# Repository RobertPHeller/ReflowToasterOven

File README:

This project is based on the Instructables "Hack a Toaster Oven for Reflow
Soldering" by frank26080115 at
https://www.instructables.com/id/Hack-a-Toaster-Oven-for-Reflow-Soldering/

Notable differences:

1) It uses an ArduinoUno as the processing element and all of the electronics 
(except the display, pushbuttons, buzzer, and relay) are mounted on an 
Adafruit Proto Shield -- all of the components are through-hole components.

There is a KiCAD project here. It includes a "four layer" board. Actually I
have no intention of creating a "four layer" PCB. I intend to build this on an
Adafruit protoshield (Product #2077). The PCB I "designed" with KiCAD is a
mock up for the Adafruit protoshield (almost). The red and green layers
represent the wiring already on the protoshield, and includes the bus strips.
The blue and white "layers" represent the added wiring. The board also
provides the approximate component placement. For those people without KiCAD
installed, I have included a PDF of the schematic in the file
ReflowToasterOven.pdf and some "pictures" of the board in the BoardPictures
folder (one is a screen shot of the KiCAD PCB layout and the others are from
the 3D viewer).

2) Everything is mounted in a pair of plastic boxes and instead of "hacking"
an extension code, an AC power entry module and a pair of AC Receptacles are
used.

There are three files related to the mechanical construction:

ReflowToasterOven-mech.tcl
ReflowToasterOven-mech.gcad
ReflowToasterOven-mech.dxf

ReflowToasterOven-mech.tcl is a Tcl program that generates the 
ReflowToasterOven-mech.gcad file, which is the input for the GCAD3D program.  
The ReflowToasterOven-mech.dxf is a DXF file, that can be imported to any 3D 
cad program.

3) An Adafruit 1.8" *Color* TFT LCD SPI display is used, using Adafruit's 
graphics library.

4) The software is a "standard" Arduino project.

And the code lives in the ReflowToasterOven subdirectory. It compiles
successfully and just fits in the Uno's flash memory and only 1/2 of the SRAM
is used by static variables, leaving just under 1K for dynamic variables.

You will need to install the Adafruit ST7735 and Adafruit_GFX libraries from 
Adafruit's GitHub repo.  You will also need the MsTimer2 library 
(http://www.pjrc.com/teensy/td_libs_MsTimer2.html).

*Most* of the code is copied from the original program by frank26080115.  I 
modified things to use C++ classes and adapted to use the Arduino I/O 
libraries, the Adafruit ST7735-based TFT display and the MsTimer2 library.

I have not built or tested it yet.

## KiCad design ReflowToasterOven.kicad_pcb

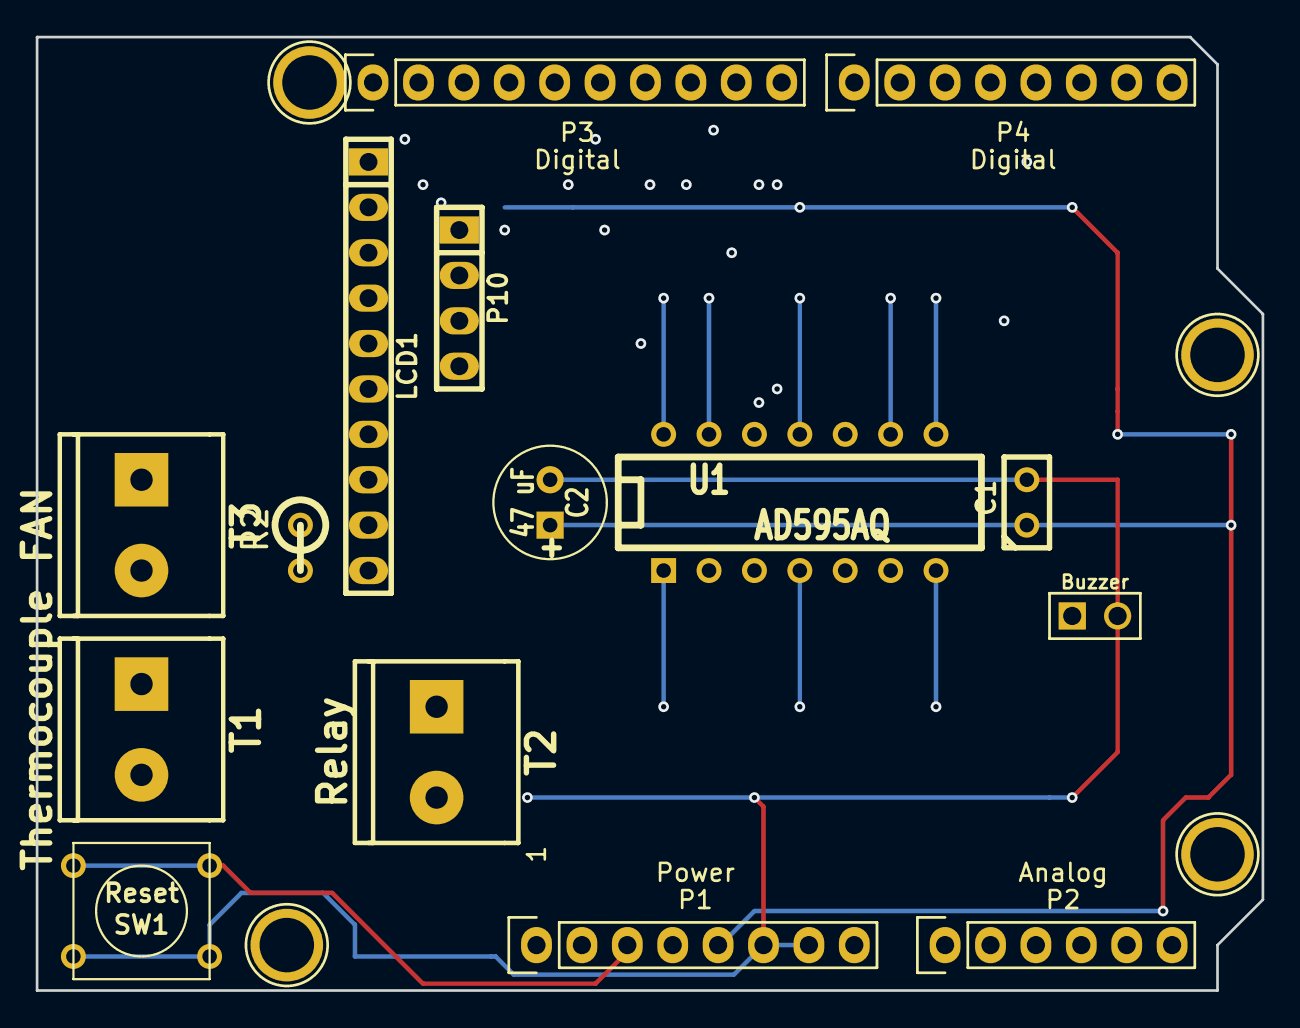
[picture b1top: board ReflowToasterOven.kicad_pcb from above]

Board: 4 copper layers, 68.6 x 53.3 mm, 19 parts (0 on the bottom side), 21 nets.

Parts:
C1: .1 uF; C1
C2: 47 uF; C1V7
LCD1: 160X128_TFT_DISPLAY; pin_strip_10
P1: Power; Socket_Strip_Arduino_1x08
P2: Analog; Socket_Strip_Arduino_1x06
P3: Digital; Socket_Strip_Arduino_1x10
P4: Digital; Socket_Strip_Arduino_1x08
P5, P6, P7, P8: CONN_01X01; Arduino_1pin
P9: Buzzer; PIN_ARRAY_2X1
P10: Switches; pin_strip_4
R2: 10K Ohms; R1
SW1: Reset; SW_PUSH_SMALL
T1: Thermocouple; mors_2p
T2: Relay; mors_2p
T3: FAN; mors_2p
U1: AD595AQ; DIP-14__300

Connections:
+3.3V: P1.4, P3.3
+5V: C1.1, C2.1, LCD1.9, P1.5, T3.1, U1.11
/A4(SDA): P2.5, P3.2
/A5(SCL): P2.6, P3.1
/Buzzer: P4.6, P9.1
/D/C: LCD1.7, P3.10
/Lite: LCD1.1, P4.5
/MISO: LCD1.2, P3.6
/MOSI: LCD1.4, P3.7
/Relay_Ctrl: P4.1, R2.1, T2.1
/Reset: P1.3, SW1.2
/SCK: LCD1.3, P3.5
/Switch1: P4.2, P10.1
/Switch2: P4.3, P10.2
/Switch3: P4.4, P10.3
/TFT_CS: LCD1.5, P3.8
/TFT_Reset: LCD1.8, P3.9
/Temp_Out: P2.1, U1.8, U1.9
GND: C1.2, C2.2, LCD1.10, P1.6, P1.7, P3.4, P9.2, P10.4, R2.2, SW1.1, T2.2, T3.2, U1.4, U1.7, U1.13
unnamed: T1.1, U1.1
unnamed: T1.2, U1.14

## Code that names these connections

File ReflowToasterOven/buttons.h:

// -!- c++ -!- //////////////////////////////////////////////////////////////
//
//  System        : 
//  Module        : 
//  Object Name   : $RCSfile$
//  Revision      : $Revision$
//  Date          : $Date$
//  Author        : $Author$
//  Created By    : Robert Heller
//  Created       : Sat Mar 24 13:23:58 2018
//  Last Modified : <180326.1313>
//
//  Description	
//
//  Notes
//
//  History
//	
/////////////////////////////////////////////////////////////////////////////
//
//    Copyright (C) 2018  Robert Heller D/B/A Deepwoods Software
//    (Portions Copyright (C) 2011 Frank Zhao)
//			51 Locke Hill Road
//			Wendell, MA 01379-9728
//
//    This program is free software; you can redistribute it and/or modify
//    it under the terms of the GNU General Public License as published by
//    the Free Software Foundation; either version 2 of the License, or
//    (at your option) any later version.
//
//    This program is distributed in the hope that it will be useful,
//    but WITHOUT ANY WARRANTY; without even the implied warranty of
//    MERCHANTABILITY or FITNESS FOR A PARTICULAR PURPOSE.  See the
//    GNU General Public License for more details.
//
//    You should have received a copy of the GNU General Public License
//    along with this program; if not, write to the Free Software
//    Foundation, Inc., 675 Mass Ave, Cambridge, MA 02139, USA.
//
// 
//
//////////////////////////////////////////////////////////////////////////////

#ifndef __BUTTONS_H
#define __BUTTONS_H
#define button_debounce_us(x) delayMicroseconds(x)
#define button_debounce_ms(x) delay(x)
#define button_debounce() delayMicroseconds(100)

#define SWITCH3 4 /* |     */ 
#define SWITCH2 5 /*  } Push buttons (DigitalRead()) */
#define SWITCH1 6 /* |     */

#define buttons_init() do{ \
pinMode(SWITCH1, INPUT_PULLUP); \
pinMode(SWITCH2, INPUT_PULLUP); \
pinMode(SWITCH3, INPUT_PULLUP); \
}while(0);

#define button_up() (digitalRead(SWITCH3) == 0)
#define button_mid() (digitalRead(SWITCH2) == 0)
#define button_down() (digitalRead(SWITCH1) == 0)

#endif // __BUTTONS_H

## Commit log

2018-03-25 Release 0.0
2018-03-25 Update mechanical drawings.
2018-03-25 Added README, LICENSE, and COPYING files.
2018-03-25 Items missing from parts list, minor fix to PC board.
2018-03-25 PDF of Schematic, images of the circuitboard.
2018-03-25 Minor tweaks to the firmware: programable colors, added in buzzer, removed unneeded include.
2018-03-25 Update README with additional details.
2018-03-26 Update Copyright and minor code rearangements.
2018-03-26 Code tweaks: embed the temp sensor and heating element in proper C++ classes and eleminate almost all of the loose global variables.
2018-03-26 Create 2D Mech drawings.
2018-03-26 Add in call to analogReference()!
2018-04-01 Remove extra comma in ReflowToasterOven/Menu.h
